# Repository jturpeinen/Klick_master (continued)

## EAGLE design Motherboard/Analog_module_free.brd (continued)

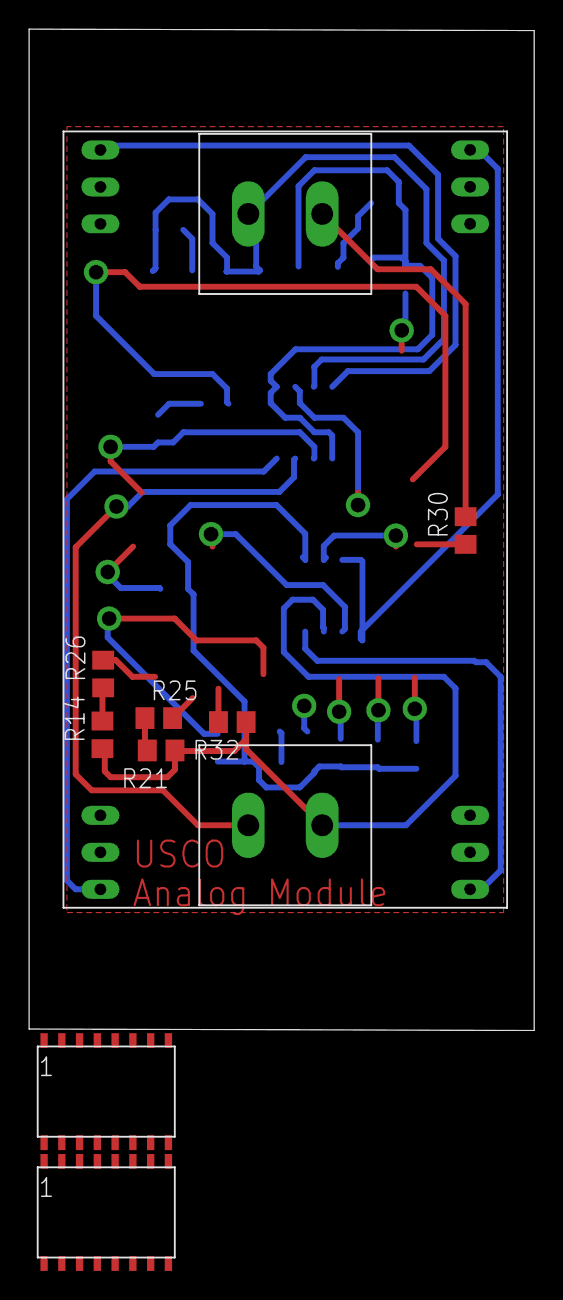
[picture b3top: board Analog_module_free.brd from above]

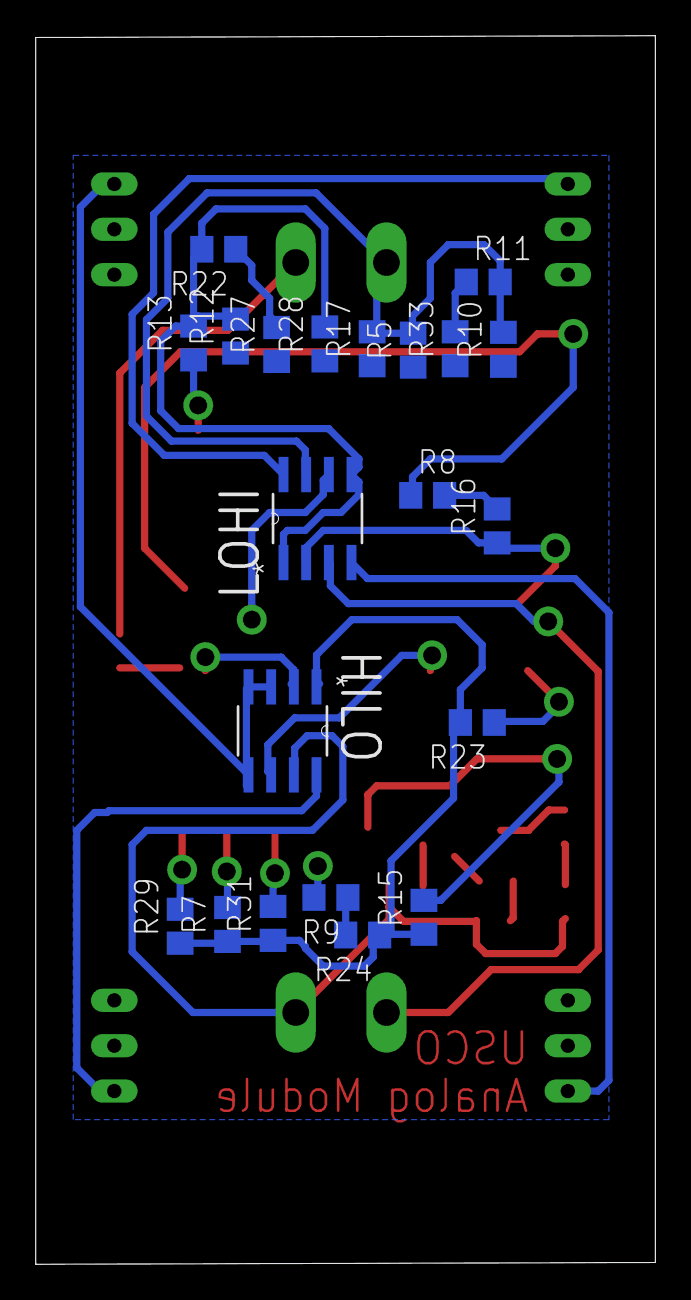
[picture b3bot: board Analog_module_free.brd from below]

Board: 2 copper layers, 34.7 x 68.8 mm, 32 parts (21 on the bottom side), 20 nets.

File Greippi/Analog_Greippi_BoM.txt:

Partlist exported from C:/Users/PAJA/Documents/eagle/Uadi-voleco/Klick_master/Greippi/Analog_Greippi.sch at 19.7.2016 9:58

Qty Value   Device     Package            Parts             Description               
4   10k     R-US_R0805 R0805              R8, R16, R23, R30 RESISTOR, American symbol 
1   110k    R-US_R0805 R0805              R28               RESISTOR, American symbol 
3   120k    R-US_R0805 R0805              R10, R31, R32     RESISTOR, American symbol 
1   15k     R-US_R0805 R0805              R29               RESISTOR, American symbol 
1   1k      R-US_R0805 R0805              R14               RESISTOR, American symbol 
1   20      R-US_R0805 R0805              R13               RESISTOR, American symbol 
1   24k     R-US_R0805 R0805              R17               RESISTOR, American symbol 
3   30k     R-US_R0805 R0805              R5, R12, R15      RESISTOR, American symbol 
1   390     R-US_R0805 R0805              R24               RESISTOR, American symbol 
1   39k     R-US_R0805 R0805              R26               RESISTOR, American symbol 
1   3k      R-US_R0805 R0805              R22               RESISTOR, American symbol 
2   3k9     R-US_R0805 R0805              R21, R33          RESISTOR, American symbol 
1   47k     R-US_R0805 R0805              R27               RESISTOR, American symbol 
2   56k     R-US_R0805 R0805              R11, R25          RESISTOR, American symbol 
1   7k5     R-US_R0805 R0805              R7                RESISTOR, American symbol 
1   8k2     R-US_R0805 R0805              R9                RESISTOR, American symbol 
2   LM358DR LM358DR    SOIC127P600X175-8N HILO, LOHI        OPERATIONAL AMPLIFIERS    
2   SWS008  SWS008     SMS-008            S2, S5            SMD Dip Switch 8 pol.

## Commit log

2016-07-06 :octocat: Added .gitattributes & .gitignore files
2016-07-06 Add test file
2016-07-06 Add "Appelsiini" schematic, board & library
2016-07-06 Move files to subdirectory
2016-07-06 Add completed "Appelsiini" schematic & board
    adds "Appelsiini" schematic, board & 11-pin connector library used on the board.
2016-07-06 add correction to "Appelsiini" board
    adds tolerance to one connection
2016-07-07 Add sub-directory Meloni
    Add Meloni version sub-directory including the versions eaglefiles.
2016-07-07 Add Input-Voltage Componentlist
    Added Textfile including the components used in the Input-Voltage regulator circuits.
2016-07-07 add correction to "Appelsiini" board
    gives more space around the board for easier matching of board sides.
2016-07-07 Add schematics for earlier versions
2016-07-08 Add subdirectory Lime-Lemon
    Added subdirectory for the Lime-Lemon model. Including an empty
    schematic file to be filled.
2016-07-08 Clean projectdirectory and add datasheets
2016-07-08 Add Appelssiini boost converter schematic
2016-07-08 Add Appelssiini boost converter board
2016-07-11 begin lime-lemon schematic and board
2016-07-11 Creates version "lime-lemon"
    includes lime-lemon schematic, board and two custom libraries.
2016-07-12 Add new lime-lemon board, schematic and inductor library
2016-07-12 Add prober inductor library
2016-07-12 Add new lime-lemon set
2016-07-13 Update repository, unkown changes
    This update is a backup done to make sure that the repository is up to
    date. Because of problems using GitHub, this update is crusial.
2016-07-13 adds corrections to lime-lemon
2016-07-13 add negative voltage booster to lime-lemon
2016-07-13 Finishes the lime-lemon board
    makes the lime-lemon board complete and ready for manufacturing
2016-07-14 Splits lime-lemon board and schematics.
2016-07-21 Creates motherboard and digital module
    Creates first schematics and board of the UADIVOLECO motherboard with positive and negative boosts, 2 places for modules and the generation of high and low digital references. Also creates schematic 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
2016-07-27 Add project website
2016-07-28 Add new version of website
2016-07-28 Add website.2
2016-07-28 Add website 0.3
2016-08-07 Add final version files
2016-08-11 Create gh-pages branch via GitHub
